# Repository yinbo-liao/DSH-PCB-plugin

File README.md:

# DSH PCB Plugin

A **DeepSeek Harness plugin** that turns PCB design into verifiable work: typed work packets, a
hash-chained evidence ledger, an independent gate monitor, and a deterministic geometry DRC.

It does not draw your board. It decides whether a board **may** proceed - and refuses when it
cannot prove it. That is the part that separates a demo from something you would send to a fab.

```
request -> S0 requirements -> S1 architecture -> S2 targets -> S3 tools
        -> S4 plan -> S5 risk & gap -> S6 layout -> G4 fabrication readiness
                 every gate signed by the monitor, never by the producer
```

## Install

Through the Plugin Manager (recommended), pointing at this repository:

```
plugin_manager install_bundle  ->  https://github.com/yinbo-liao/DSH-PCB-plugin
```

Or link a checkout for development:

```sh
git clone https://github.com/yinbo-liao/DSH-PCB-plugin
cd DSH-PCB-plugin
node --test "test/*.test.js"
```

The package declares `dsh.bundle.patch`, so installing it inserts the `dsh-pcb` plugin row into
the host composition (`cordis.patch.yml`), and the tools appear on the next mount.

### Configuration

Every tool takes explicit paths, so no configuration is required. The plugin row may set
defaults:

```yaml
- insert:
    - id: dsh-pcb
      name: '@yinbo-liao/dsh-pcb'
      config:
        runDir: runs/board-a
        boardDir: boards/board-a
        kicadPath: 'C:/Program Files/KiCad/9.0/bin/kicad-cli.exe'
```

## Tools

| Tool | Purpose |
|---|---|
| `pcb_init` | Create the run: artifact index + evidence ledger, and optionally record the ruleset baseline |
| `pcb_baseline` | Record `hw/board.kicad_dru` as the DRC baseline; **refuses to overwrite** without `force` |
| `pcb_register` | Hash an artifact file and bind it to a stage and a producing role |
| `pcb_approve` | Record a human approval bound to the artifact hash; editing the artifact voids it |
| `pcb_packet_open` | Open a typed packet: enforces stage order, budgets, role tool scope and input hashes |
| `pcb_packet_close` | Close a packet; outputs must be produced by that role, in that role's scope |
| `pcb_verify` | Run the monitor over G0-G4, record evidence, return PASS / HOLD / REFUSED |
| `pcb_export` | Generate the `.kicad_pcb` from the board model (rotation and text offsets included) |
| `pcb_geometry_drc` | Deterministic subset DRC: clearance, track width, annular ring, edge, floating pads |
| `pcb_trial_test` | S7: turn bench measurements (CSV) into per-criterion verdicts, write `RESULTS.json`, report coverage |
| `pcb_trace` | Requirement traceability matrix and `match_score` |
| `pcb_doctor` | Ledger chain, hash drift, toolkit availability, gate set |

### What the gates check

| Gate | Signs off |
|---|---|
| G0 scope frozen | requirements with numeric thresholds, non-goals, envelope, assumptions, human approval |
| G1 architecture and parts | power budget with margin, derating, BOM lines resolved |
| G2 targets, tools, plan | every must-have has a criterion; every gate check maps to a deterministic tool |
| G3 risk and gap closure | risks at RPN >= 60 mitigated; no missing or contradicted requirement |
| G4 fabrication readiness | kicad-cli DRC (error-level verdict, warnings triaged), geometry DRC, netlist parity, positional export parity, footprint record, unmodified ruleset |
| G5 trial test executed | every criterion measured with a value and an instrument; `not_run` holds the gate |
| G6 results evaluated | execution-phase traceability: nothing unverified, `match_score` >= 0.90 |

## Quick start with the bundled example

`examples/ldo3v3/` is a real 5 V to 3.3 V, 300 mA, two-layer supply board (12 parts), authored
as a netlist plus a board model.

```js
pcb_init      { runDir: 'runs/a', board: 'LDO3V3', boardDir: 'examples/ldo3v3' }
pcb_register  { runDir: 'runs/a', id: 'REQ', path: 'examples/ldo3v3/REQ.json', stage: 'S0', producer: 'requirements-analyst' }
pcb_register  { ... }                       // ARCH, POWER, BOM, TARGETS, TOOLS, RISK, GAP, PCB, NETLIST ...
pcb_approve   { runDir: 'runs/a', artifact: 'REQ', approver: 'you' }
pcb_verify    { runDir: 'runs/a', boardDir: 'examples/ldo3v3', until: 'G4' }
```

Outcome on a machine **with** KiCad 10.0.8 (`--kicad <path>`):

```
G0 scope frozen                  PASS
G1 architecture and parts        PASS
G2 targets, tools, plan          PASS
G3 risk and gap closure          PASS
G4 fabrication readiness         PASS   kicad-cli pcb drc: 0 errors, 12 warnings triaged
  B2_kicad_drc          pass      DRC 0 errors
  B2g_geometry          pass      0 violations across 5 checks
  B3g_netlist_parity    pass      5 nets, 23 pads
  B3x_export_parity     pass      export matches model (50 items)
  C7_footprint_record   pass      7 footprints verified
  B4_ruleset            pass      ruleset matches baseline
S7 trial test                     not_run - no board fabricated, 7 criteria unmeasured
```

Without KiCad the same run records G4 as **HOLD** with `B2_kicad_drc: not_run`, which is the
correct result and not a failure of the tooling. **`not_run` is never converted to a pass.**

The verdict comes from the **error-level** DRC exit code; every warning is recorded in a second
all-severity report for triage (see `examples/ldo3v3/hw/DRC-TRIAGE.md`). Closing G4 for real
found four genuine defects in the exporter, each listed there.

A recorded run is committed in [`docs/recorded-runs/ldo3v3/`](docs/recorded-runs/ldo3v3/README.md).

### Why the generator lives here

The `.kicad_pcb` generator used to live in a separate Python project. That split is what let a
dropped placement rotation ship: the model was right, the export was wrong, and the check that
should have caught it compared counts instead of positions. Both halves now live in one package,
`pcb_export` produces the file the gate consumes, and the parity check compares every vertex to
0.01 mm.

## Trial test (S7)

`pcb_trial_test` converts measurements into verdicts **by comparison**, never by judgement:

| Measurement | Verdict |
|---|---|
| absent | `not_run` - and the gate holds |
| outside the threshold | `fail` |
| inside but within 10 % of a limit | `marginal` |
| otherwise | `pass` (value, instrument and uncertainty recorded) |

One row per criterion per board; the **worst** verdict wins, so a bad board cannot be averaged
away. The procedure, instruments and safety steps for the bundled board are in
[`examples/ldo3v3/BENCH.md`](examples/ldo3v3/BENCH.md), and the CSV template is
[`examples/ldo3v3/MEASUREMENTS.csv`](examples/ldo3v3/MEASUREMENTS.csv).

```
pcb_trial_test { runDir, boardDir: 'examples/ldo3v3', measurementsPath: 'examples/ldo3v3/MEASUREMENTS.csv' }
pcb_verify     { runDir, boardDir: 'examples/ldo3v3', until: 'G6' }
```

The template ships with empty values, so today the trial test reports `not_run` for all seven
criteria and G5 holds. That is the true state of an unbuilt board, not a missing feature.

## Artifact contract

The tools read the same JSON artifacts the companion Python harness writes, so the formats are
interchangeable:

| File | Holds |
|---|---|
| `REQ.json` | requirements: id, priority, threshold, unit, verification, design element |
| `TARGETS.json` | criteria: threshold, method, instrument, `test_planned` |
| `POWER.json` | rails, loads, margin, thermal calculation |
| `DERATE.json` | component ratings versus applied stress |
| `BOM.json` | lines with MPN, package, lifecycle, datasheet, alternates |
| `RISK.json` | risks with severity/likelihood/detectability, RPN, mitigation, residual |
| `TOOLS.json` | per-check tool, determinism, strength, blind spots, gate mapping |
| `GAP.json` | gap register and improvement plan |
| `hw/board.json` | placements, routes, vias, rules - the authoritative board model |
| `hw/netlist.json` | nets and pads - connectivity intent |
| `hw/FOOTPRINTS.json` | footprint verification record against a source |
| `hw/board.kicad_dru` | DRC ruleset, hashed as the baseline |
| `hw/board.kicad_pcb` | derived export, so KiCad can open the board and run its own DRC |

## Design rules this plugin enforces

1. **The producer never approves its own work.** `approve`, `waive` and `verify` are reserved;
   the router adds them to every producer's deny list, and the attempt is recorded.
2. **Evidence is hash-bound and goes stale.** The live release digests the files on disk, so
   editing an artifact after a gate passed invalidates that gate.
3. **Gate signatures cover only their own artifacts.** Adding a later stage does not invalidate
   an earlier gate; changing one of its inputs does.
4. **`not_run` is never `pass`.** The monitor maps a missing tool to HOLD with the blocker named.
5. **A relaxed ruleset is refused, not failed.** The baseline check distinguishes "the board is
   wrong" from "the rules were changed to make the board look right".
6. **Deterministic checks outrank model judgement.** Every gate-critical check names a tool with
   a determinism class and a strength; a weak or LLM-only check cannot close a gate.

## What is verified, and what is not

Verified by this repository's tests (47 tests):

- ledger tamper detection (edit and deletion), live release digest, freshness
- per-artifact gate digests and gate staleness
- clearance/width/annular/edge/floating-pad checks, with a real injected violation
- netlist parity, and **positional** export parity (0.01 mm): a dropped rotation or a 0.5 mm shift is caught
- the generator is deterministic and reproduces the committed export byte for byte
- approval voiding when the payload changes, ruleset refusal
- stage ordering, budgets, reserved-tool denial
- the full S0-G4 flow on the example board, including `not_run` handling
- S7 verdict derivation (pass/marginal/fail/not_run), worst-board-wins, CSV parsing
- G5 holding on an unexecuted trial test, and G6 requiring full coverage at release
- every tool spec compiles through the **real** `@deepseek-ai/dsh-tools` `defineTool`
- against a real `kicad-cli` (set `DSH_KICAD_PATH`): 0 DRC errors on the example board, with the
  version and warning count recorded; a missing tool stays `not_run`

Not verified - stated plainly:

- **kicad-cli DRC against a real KiCad install.** The adapter is exercised through its decision
  table and a mocked exit code; the suite expects `not_run` when KiCad is absent.
- **KiCad loadability of the exported `.kicad_pcb`.** The export is checked against the model by
  this repository's own s-expression reader, not by KiCad.
- **Signal integrity, power integrity, EMC, impedance control.** No tool here can see them; the
  checks are labelled `medium` strength and the gate set names what it checks.
- **Supplier existence of BOM MPNs.** There is no parts API; `C5` verifies that the record is
  complete, not that the part is in stock.

## Status of the two blockers

1. **KiCad: resolved.** A KiCad 10.0.8 install at `Y:\kicad` was pointed at with `--kicad`, and
   **G4 now passes** with a real `kicad-cli pcb drc` (0 errors). Installing it from this session
   was impossible - see [`BLOCKERS.md`](BLOCKERS.md) for the probe evidence - so the run depends on
   the operator supplying the path. The adapter no longer uses piped stdio (a sandbox refuses
   those), and records warnings separately from the error verdict.
2. **No physical board: open.** S7 has no real measurements, so every criterion is `not_run` and
   `examples/ldo3v3/MEASUREMENTS.csv` is deliberately empty. `pcb_trial_test` derives verdicts
   the moment those numbers exist.

## Development

```sh
node --test "test/*.test.js"                                  # normal machines
node --test --test-isolation=none "test/*.test.js"            # restricted sandboxes
DSH_TOOLS_PATH=file:///path/to/dsh-tools/lib/index.js node test/sdk.integration.test.js
```

The SDK integration test skips itself when the module is unavailable, so the suite stays green
in a plain checkout while still proving compatibility where DSH is installed.

## Layout

```
index.js              plugin entry: apply(ctx, config) -> disposer
src/plugin.js         the ten tools
src/config.js         stages, roles, budgets, gate artifacts, envelope
src/core.js           artifact store + hash-chained ledger
src/router.js         packets, scopes, budgets, gate staleness
src/checks.js         Class A / B / C checks
src/geom.js           geometry engine + .kicad_pcb reader (rotation-aware)
src/boardgen.js       board model -> .kicad_pcb export
src/parity.js         netlist <-> board <-> export
src/kicad.js          kicad-cli adapter (fails closed)
src/gates.js          gate table, monitor, verdict, report
src/trace.js          traceability matrix and match score
src/trial.js          S7 measurements -> verdicts
examples/ldo3v3/      a complete example board and its artifacts
test/                 47 tests, including red-team cases and the positional-parity cases
scripts/record-run.mjs replay the example and record runs/TRANSCRIPT.json
BLOCKERS.md           what this environment cannot do, and what unblocks it
```

## Related

The design this implements - stage contracts, evidence discipline, red-team cases - is in the
companion knowledge base, `09-agent/` (agent specification, monitor charter, trial test
protocol). This plugin is the executable subset of that design.

## Licence

MIT.

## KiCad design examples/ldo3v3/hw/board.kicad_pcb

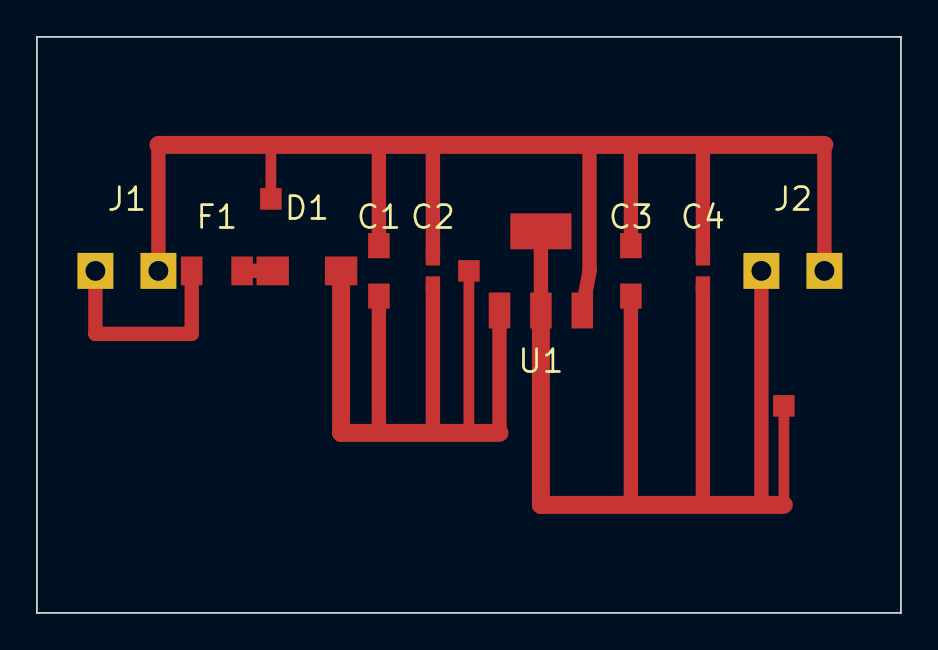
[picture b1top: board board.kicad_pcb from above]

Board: 2 copper layers, 48.0 x 32.0 mm, 12 parts (0 on the bottom side), 5 nets.

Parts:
C1, C3: C_1206_V
C2, C4: C_0603_V
D1: D_SMA
F1: R_1206
J1, J2: TERM_1x02
TP1, TP2, TP3: TP_1PAD
U1: U_SOT223

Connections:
3V3: C3.2, C4.2, J2.1, TP2.1, U1.2, U1.4
5V: C1.2, C2.2, D1.2, TP1.1, U1.3
GND: C1.1, C2.1, C3.1, C4.1, J1.2, J2.2, TP3.1, U1.1
VIN: F1.1, J1.1
VIN_F: D1.1, F1.2
